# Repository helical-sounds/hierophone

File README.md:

# Hierophone

The Hierophone is an instrument designed around resonating a sheet of metal by placing it in an audio feedback loop. By changing the filtering of the audio, the phase and level of feedback, and manipulating the sheet directly, different overtones and sounds can be generated.

The name derives from ancient Greek, being the combination of ἱερά (hiera, 'holy') and φωνή (phōnē, 'voice'), together meaning "Holy Voice".

## Contact

Drop me an email at guy@rumblesan.com

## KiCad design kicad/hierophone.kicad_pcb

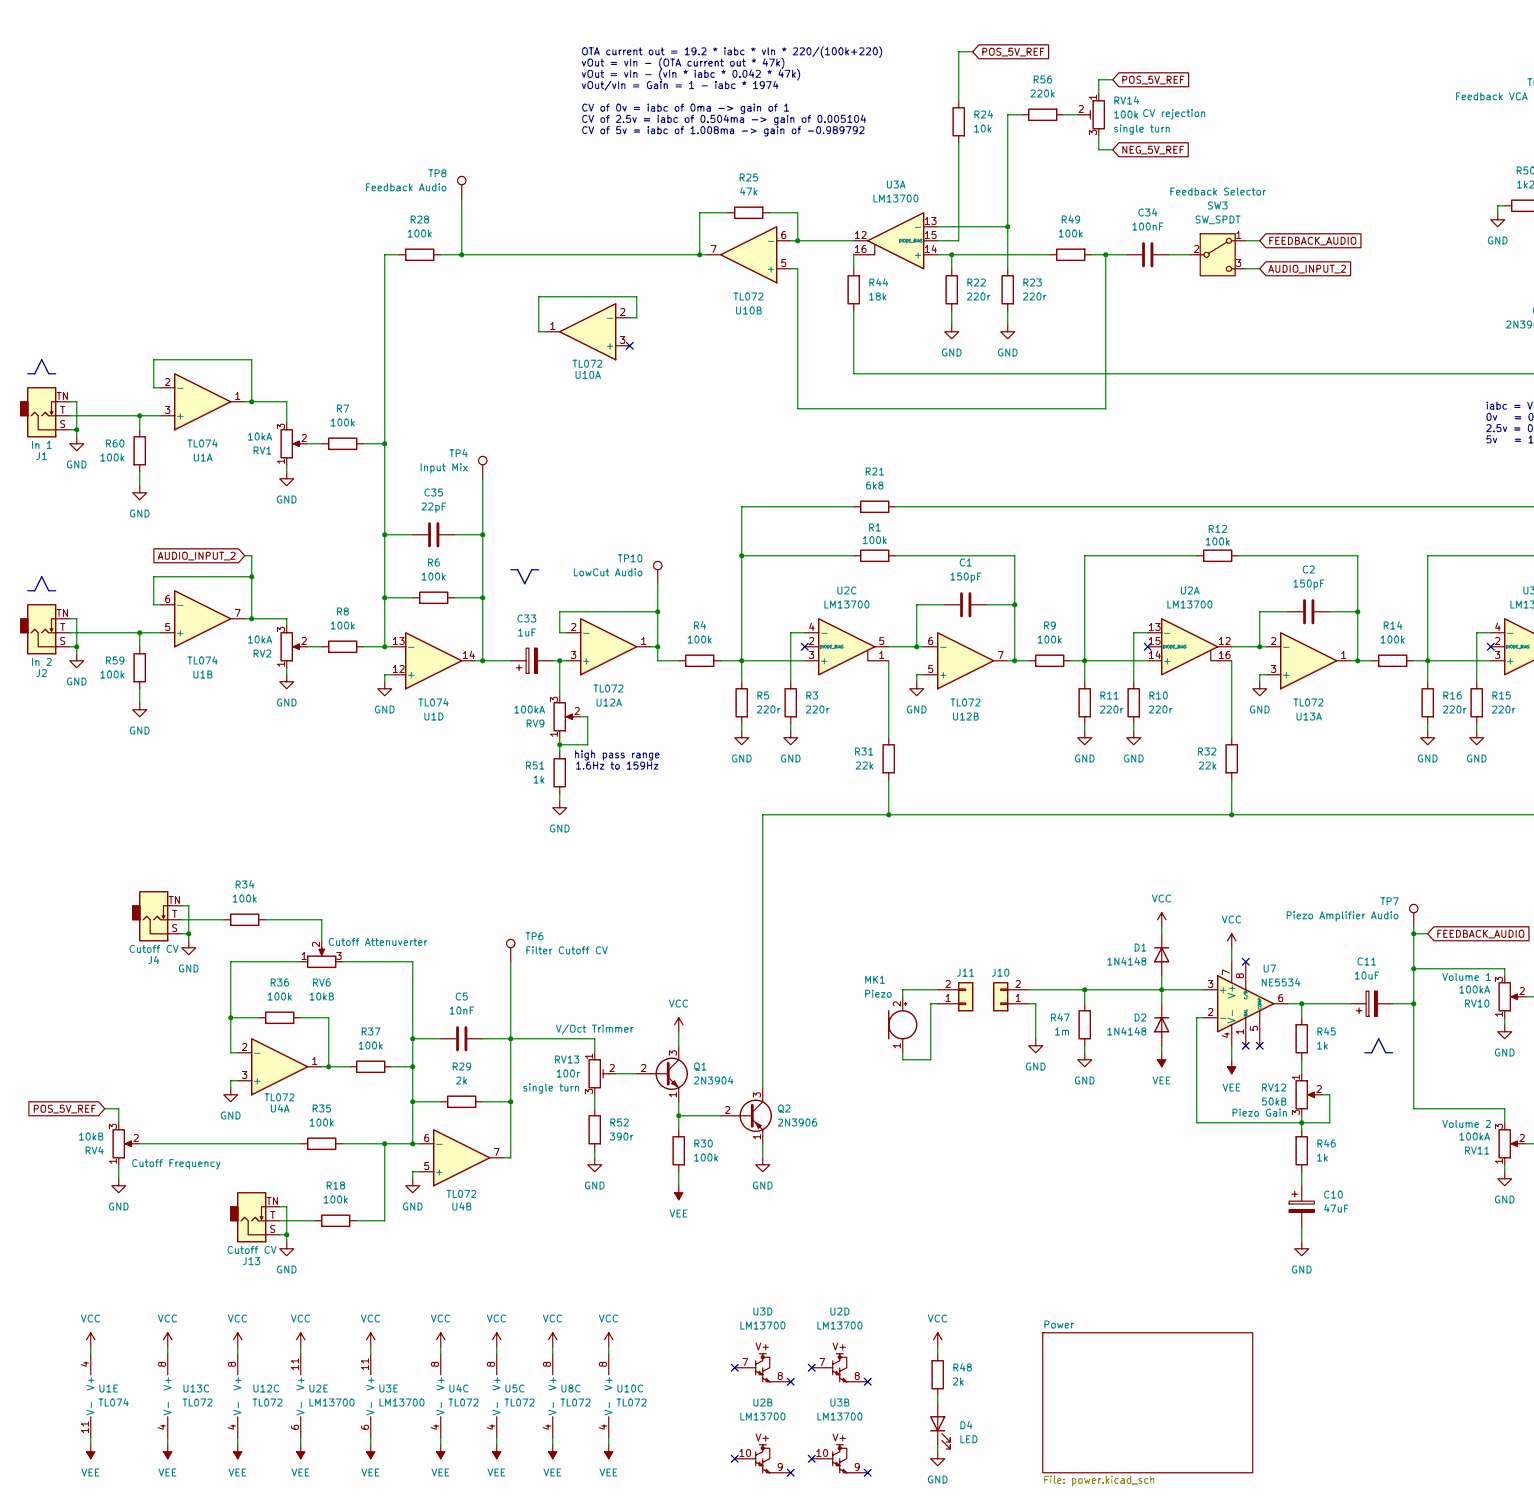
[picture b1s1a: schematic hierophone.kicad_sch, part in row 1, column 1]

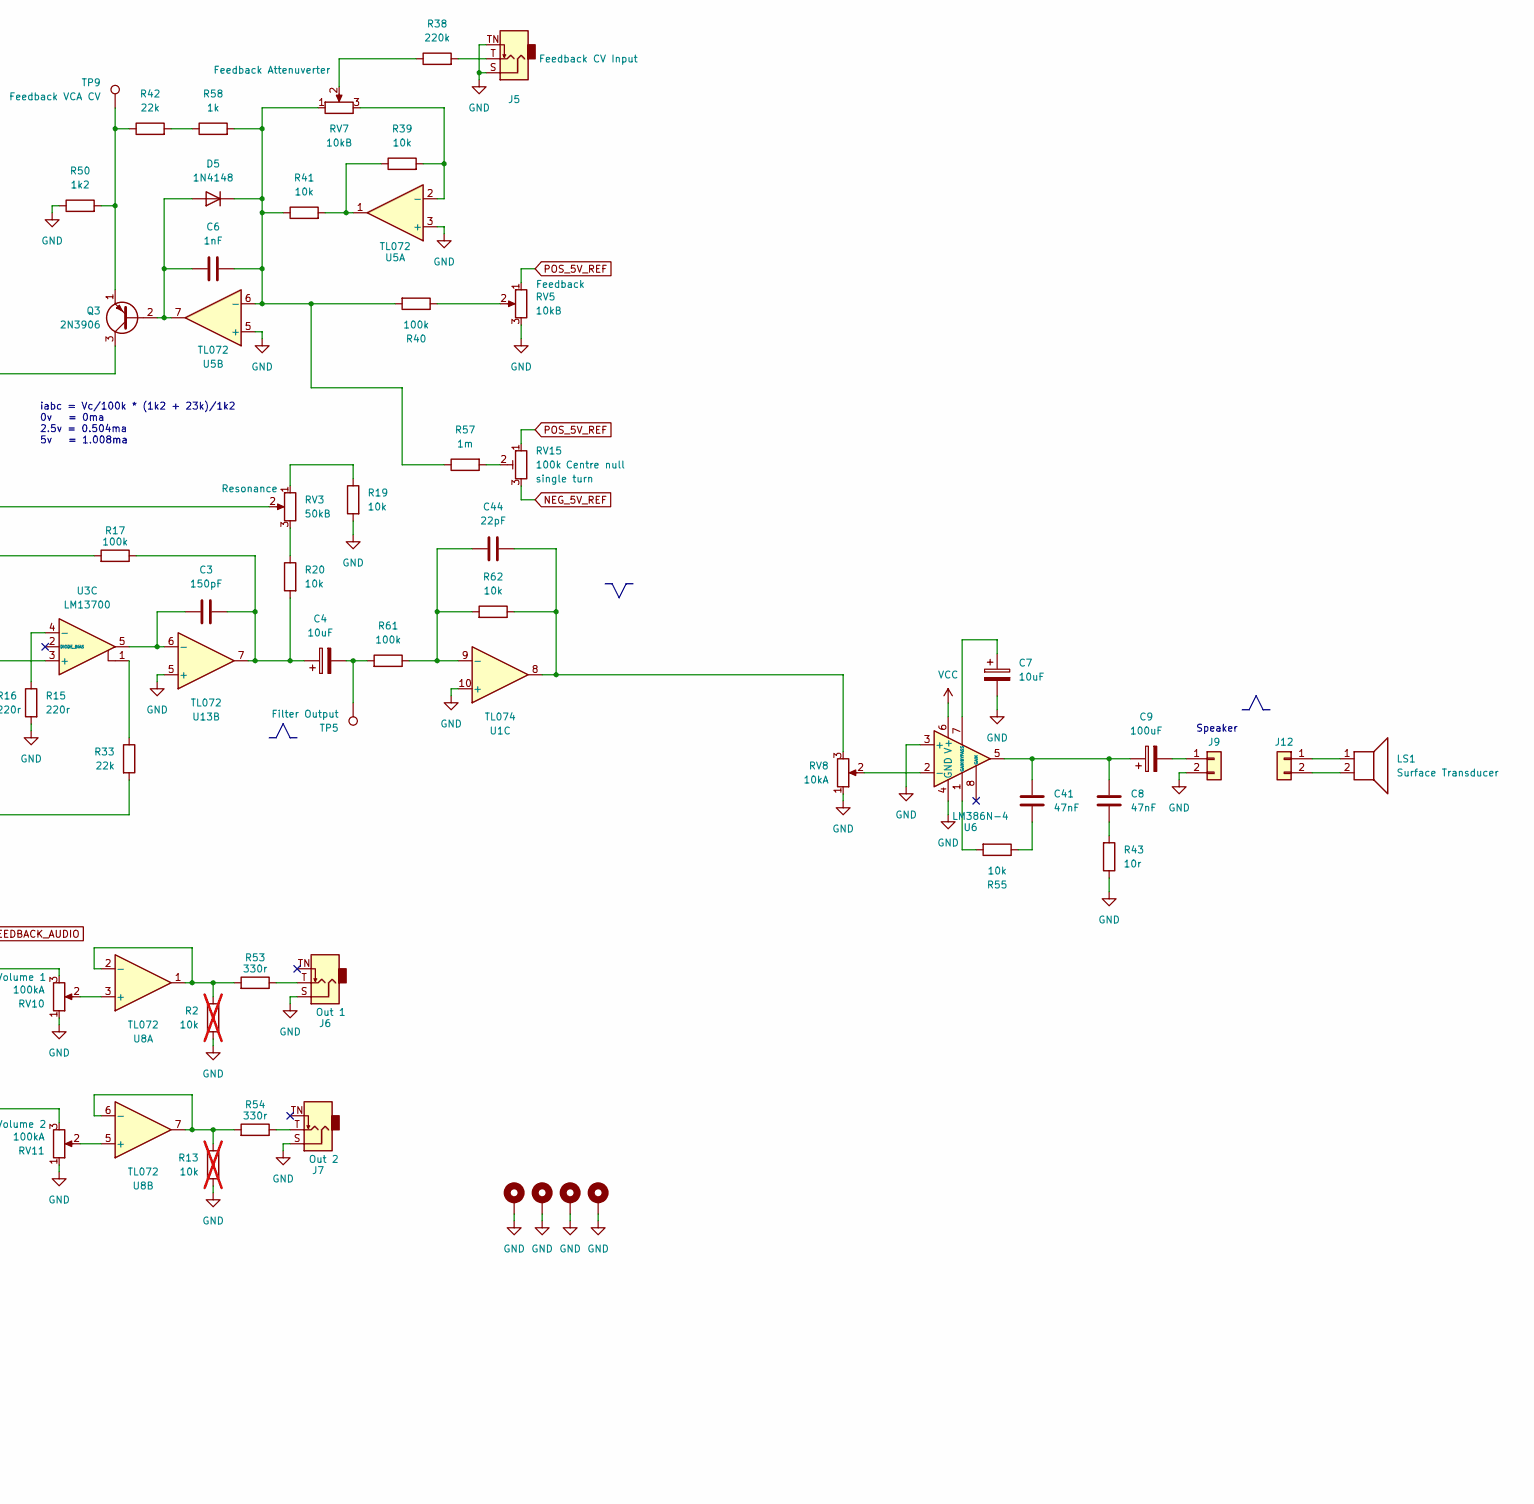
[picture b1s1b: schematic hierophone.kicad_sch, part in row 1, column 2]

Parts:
C1, C2, C3: 150pF; C_Rect_L7.0mm_W4.5mm_P5.00mm; Tolerance 5%
C4, C7, C11: 10uF; CP_Radial_D5.0mm_P2.00mm; Tolerance 20%; Voltage 50v
C5: 10nF; C_Rect_L7.0mm_W2.5mm_P5.00mm; Tolerance 5%
C6: 1nF; C_Rect_L7.0mm_W2.5mm_P5.00mm; Tolerance 5%
C8, C41: 47nF; C_Rect_L7.0mm_W2.5mm_P5.00mm; Tolerance 5%
C9: 100uF; CP_Radial_D5.0mm_P2.00mm; Tolerance 20%; Voltage 50v
C10: 47uF; CP_Radial_D5.0mm_P2.00mm; Tolerance 20%; Voltage 50v
C33: 1uF; CP_Radial_D5.0mm_P2.00mm; Tolerance 20%; Voltage 50v
C34: 100nF; C_Rect_L7.0mm_W2.5mm_P5.00mm; Tolerance 5%
C35, C44: 22pF; C_Rect_L7.0mm_W2.5mm_P5.00mm; Tolerance 5%
D1, D2, D5: 1N4148; D_DO-35_SOD27_P7.62mm_Horizontal
D4: LED; LED_D5.0mm
H1, H2, H3, H4: MountingHole_Pad; MountingHole_3.2mm_M3_Pad
J1, J2, J4, J5, J6, J7, J13: AudioJack2_SwitchT; Jack_3.5mm_QingPu_WQP-PJ398SM_Vertical
J9, J10, J11, J12: Conn_01x02; Molex_KK-254_22-05-7028_1x02_P2.54mm_Horizontal
LS1: Surface Transducer
MK1: Piezo; PinHeader_1x02_P2.54mm_Vertical
Q1: 2N3904; TO-92_Inline_Wide
Q2, Q3: 2N3906; TO-92_Inline_Wide
R1, R4, R6, R7, R8, R9, R12, R14, R17, R18, R28, R30, R34, R35, R36, R37, R40, R49, R59, R60, R61: 100k; R_Axial_DIN0207_L6.3mm_D2.5mm_P10.16mm_Horizontal; Tolerance 1%
R2, R13: 10k; R_Axial_DIN0207_L6.3mm_D2.5mm_P10.16mm_Horizontal; Tolerance 1%; not fitted
R3, R5, R10, R11, R15, R16, R22, R23: 220r; R_Axial_DIN0207_L6.3mm_D2.5mm_P10.16mm_Horizontal; Tolerance 1%
R19, R20, R24, R39, R41, R55, R62: 10k; R_Axial_DIN0207_L6.3mm_D2.5mm_P10.16mm_Horizontal; Tolerance 1%
R21: 6k8; R_Axial_DIN0207_L6.3mm_D2.5mm_P10.16mm_Horizontal; Tolerance 1%
R25: 47k; R_Axial_DIN0207_L6.3mm_D2.5mm_P10.16mm_Horizontal; Tolerance 1%
R29, R48: 2k; R_Axial_DIN0207_L6.3mm_D2.5mm_P10.16mm_Horizontal; Tolerance 1%
R31, R32, R33, R42: 22k; R_Axial_DIN0207_L6.3mm_D2.5mm_P10.16mm_Horizontal; Tolerance 1%
R38, R56: 220k; R_Axial_DIN0207_L6.3mm_D2.5mm_P10.16mm_Horizontal; Tolerance 1%
R43: 10r; R_Axial_DIN0207_L6.3mm_D2.5mm_P10.16mm_Horizontal; Tolerance 1%
R44: 18k; R_Axial_DIN0207_L6.3mm_D2.5mm_P10.16mm_Horizontal; Tolerance 1%
R45, R46, R51, R58: 1k; R_Axial_DIN0207_L6.3mm_D2.5mm_P10.16mm_Horizontal; Tolerance 1%
R47, R57: 1m; R_Axial_DIN0207_L6.3mm_D2.5mm_P10.16mm_Horizontal; Tolerance 1%
R50: 1k2; R_Axial_DIN0207_L6.3mm_D2.5mm_P10.16mm_Horizontal; Tolerance 1%
R52: 390r; R_Axial_DIN0207_L6.3mm_D2.5mm_P10.16mm_Horizontal; Tolerance 1%
R53, R54: 330r; R_Axial_DIN0207_L6.3mm_D2.5mm_P10.16mm_Horizontal; Tolerance 1%
RV1, RV2, RV8: 10kA; Potentiometer_Alpha_RD901F-40-00D_Single_Vertical
RV3, RV12: 50kB; Potentiometer_Alpha_RD901F-40-00D_Single_Vertical
RV4, RV5, RV6, RV7: 10kB; Potentiometer_Alpha_RD901F-40-00D_Single_Vertical
RV9, RV10, RV11: 100kA; Potentiometer_Alpha_RD901F-40-00D_Single_Vertical
RV13: 100r; Potentiometer_THT_Bourns_3306P_Vertical
RV14, RV15: 100k; Potentiometer_THT_Bourns_3306P_Vertical
SW3: SW_SPDT; Toggle_Switch_100SP-M2
TP4: Input Mix; TestPoint_Loop_D2.50mm_Drill1.0mm_LowProfile
TP5: Filter Output; TestPoint_Loop_D2.50mm_Drill1.0mm_LowProfile
TP6: Filter Cutoff CV; TestPoint_Loop_D2.50mm_Drill1.0mm_LowProfile
TP7: Piezo Amplifier Audio; TestPoint_Loop_D2.50mm_Drill1.0mm_LowProfile
TP8: Feedback Audio; TestPoint_Loop_D2.50mm_Drill1.0mm_LowProfile
TP9: Feedback VCA CV; TestPoint_Loop_D2.50mm_Drill1.0mm_LowProfile
TP10: LowCut Audio; TestPoint_Loop_D2.50mm_Drill1.0mm_LowProfile
U1: TL074; DIP-14_W7.62mm_Socket
U2, U3: LM13700; DIP-16_W7.62mm_Socket
U4, U5, U8, U10, U12, U13: TL072; DIP-8_W7.62mm_Socket
U6: LM386N-4; DIP-8_W7.62mm_Socket
U7: NE5534; DIP-8_W7.62mm_Socket

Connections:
AUDIO_INPUT_2: RV2.3, SW3.3 (C), U1.6 (-), U1.7
FEEDBACK_AUDIO: C11.2, RV10.3, RV11.3, SW3.1 (A), TP7.1
GND: C7.2, C10.2, D4.1 (K), H1.1, H2.1, H3.1, H4.1, J1.S, J1.TN, J2.S, J2.TN, J4.S, J4.TN, J5.S, J5.TN, J6.S, J7.S, J9.2, J10.1, J13.S, J13.TN, Q2.1 (E), R2.2, R3.1, R5.1, R10.1, R11.1, R13.2, R15.1, R16.1, R19.1, R22.1, R23.1, R43.2, R47.2, R50.2, R51.2, R52.1, R59.1, R60.1, RV1.1, RV2.1, RV4.1, RV5.3, RV8.1, RV10.1, RV11.1, U1.10 (+), U1.12 (+), U4.3 (+), U4.5 (+), U5.3 (+), U5.5 (+), U6.3 (+), U6.4 (GND), U12.5 (+), U13.3 (+), U13.5 (+); also elsewhere on the board
NEG_5V_REF: RV14.3, RV15.3; also elsewhere on the board
unnamed: C1.1, R1.1, R9.1, U12.7
unnamed: C2.1, R12.2, R14.1, U13.1
unnamed: C3.1, C4.1, R17.2, R20.1, U13.7
unnamed: C4.2, R61.1, TP5.1
unnamed: C5.2, R29.2, RV13.1, TP6.1, U4.7
unnamed: C8.2, R43.1
unnamed: C10.1, R46.2
unnamed: C11.1, R45.1, U7.6
unnamed: C33.1, C35.1, R6.2, TP4.1, U1.14
unnamed: C8.1, C9.1, C41.1, U6.5
unnamed: C41.2, R55.2
unnamed: C44.1, R62.2, RV8.3, U1.8
unnamed: D1.2 (A), D2.1 (K), J10.2, R47.1, U7.3 (+)
unnamed: D4.2 (A), R48.2
unnamed: C6.2, D5.2 (A), Q3.2 (B), U5.7
unnamed: C6.1, D5.1 (K), R40.1, R41.2, R57.2, R58.1, RV7.1, U5.6 (-)
unnamed: J4.T, R34.1
unnamed: J5.T, R38.1
unnamed: J6.T, R53.2
unnamed: J7.T, R54.2
unnamed: C9.2, J9.1
unnamed: J11.1, MK1.1 (-)
unnamed: J11.2, MK1.2 (+)
unnamed: J12.1, LS1.1
unnamed: J12.2, LS1.2
unnamed: J13.T, R18.1
unnamed: Q1.2 (B), RV13.2
unnamed: Q1.1 (E), Q2.2 (B), R30.2
unnamed: Q2.3 (C), R31.1, R32.1, R33.1
unnamed: Q3.3 (C), R44.2
unnamed: Q3.1 (E), R42.2, R50.1, TP9.1
unnamed: R7.1, RV1.2
unnamed: R8.1, RV2.2
unnamed: R19.2, RV3.1
unnamed: R20.2, RV3.3
unnamed: R21.2, RV3.2
unnamed: R25.2, R28.2, TP8.1, U10.7
unnamed: R31.2, U2.1
unnamed: R32.2, U2.16
unnamed: R33.2, U3.1
unnamed: R34.2, RV6.2
unnamed: R35.1, RV4.2
unnamed: R36.2, R37.1, U4.1
unnamed: R38.2, RV7.2
unnamed: R39.2, R41.1, U5.1
unnamed: R40.2, RV5.2
unnamed: R42.1, R58.2
unnamed: R44.1, U3.16
unnamed: R45.2, RV12.1
unnamed: R51.1, RV9.1, RV9.2
unnamed: R52.2, RV13.3
unnamed: R55.1, U6.1 (GAIN)
unnamed: R56.1, RV14.2
unnamed: R57.1, RV15.2
unnamed: C34.2, SW3.2 (B)
unnamed: J1.T, R60.2, U1.3 (+)
unnamed: RV1.3, U1.1, U1.2 (-)
unnamed: J2.T, R59.2, U1.5 (+)
unnamed: C44.2, R61.2, R62.1, U1.9 (-)
unnamed: C35.2, R6.1, R7.2, R8.2, R28.1, U1.13 (-)
unnamed: R9.2, R11.2, R12.1, U2.14 (+)
unnamed: R10.2, U2.13 (-)
unnamed: R1.2, R4.2, R5.2, R21.1, U2.3 (+)
unnamed: R3.2, U2.4 (-)
unnamed: R22.2, R49.2, U3.14 (+)
unnamed: R23.2, R56.2, U3.13 (-)
unnamed: R24.1, U3.15 (DIODE_BIAS)
unnamed: R14.2, R16.2, R17.1, U3.3 (+)
unnamed: R15.2, U3.4 (-)
unnamed: R36.1, RV6.1, U4.2 (-)
unnamed: C5.1, R18.2, R29.1, R35.2, R37.2, RV6.3, U4.6 (-)
unnamed: R39.1, RV7.3, U5.2 (-)
unnamed: RV8.2, U6.2 (-)
unnamed: C7.1, U6.7 (BYPASS)
unnamed: R46.1, RV12.2, RV12.3, U7.2 (-)
unnamed: RV10.2, U8.3 (+)
unnamed: R2.1, R53.1, U8.1, U8.2 (-)
unnamed: RV11.2, U8.5 (+)
unnamed: R13.1, R54.1, U8.6 (-), U8.7
unnamed: U10.1, U10.2 (-)
unnamed: C34.1, R49.1, U10.5 (+)
unnamed: R25.1, U3.12, U10.6 (-)
unnamed: C33.2, RV9.3, U12.3 (+)
unnamed: R4.1, TP10.1, U12.1, U12.2 (-)
unnamed: C1.2, U2.5, U12.6 (-)
unnamed: C2.2, U2.12, U13.2 (-)
unnamed: C3.2, U3.5, U13.6 (-)
POS_5V_REF: R24.2, RV4.3, RV5.1, RV14.1, RV15.1; also elsewhere on the board
VCC: D1.1 (K), Q1.3 (C), R48.1, U1.4 (V+), U2.11 (V+), U3.11 (V+), U4.8 (V+), U5.8 (V+), U6.6 (V+), U7.7 (V+), U8.8 (V+), U10.8 (V+), U12.8 (V+), U13.8 (V+); also elsewhere on the board
VEE: D2.2 (A), R30.1, U1.11 (V-), U2.6 (V-), U3.6 (V-), U4.4 (V-), U5.4 (V-), U7.4 (V-), U8.4 (V-), U10.4 (V-), U12.4 (V-), U13.4 (V-); also elsewhere on the board

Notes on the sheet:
high pass range 1.6Hz to 159Hz
Speaker
OTA current out = 19.2 * iabc * vIn * 220/(100k+220) vOut = vIn - (OTA current out * 47k) vOut = vIn - (vIn * iabc * 0.042 * 47k) vOut/vIn = Gain = 1 - iabc * 1974 CV of 0v = iabc of 0ma -> gain of 1 CV of 2.5v = iabc of 0.504ma -> gain of 0.005104 CV of 5v = iabc of 1.008ma -> gain of -0.989792
iabc = Vc/100k * (1k2 + 23k)/1k2 0v = 0ma 2.5v = 0.504ma 5v = 1.008ma

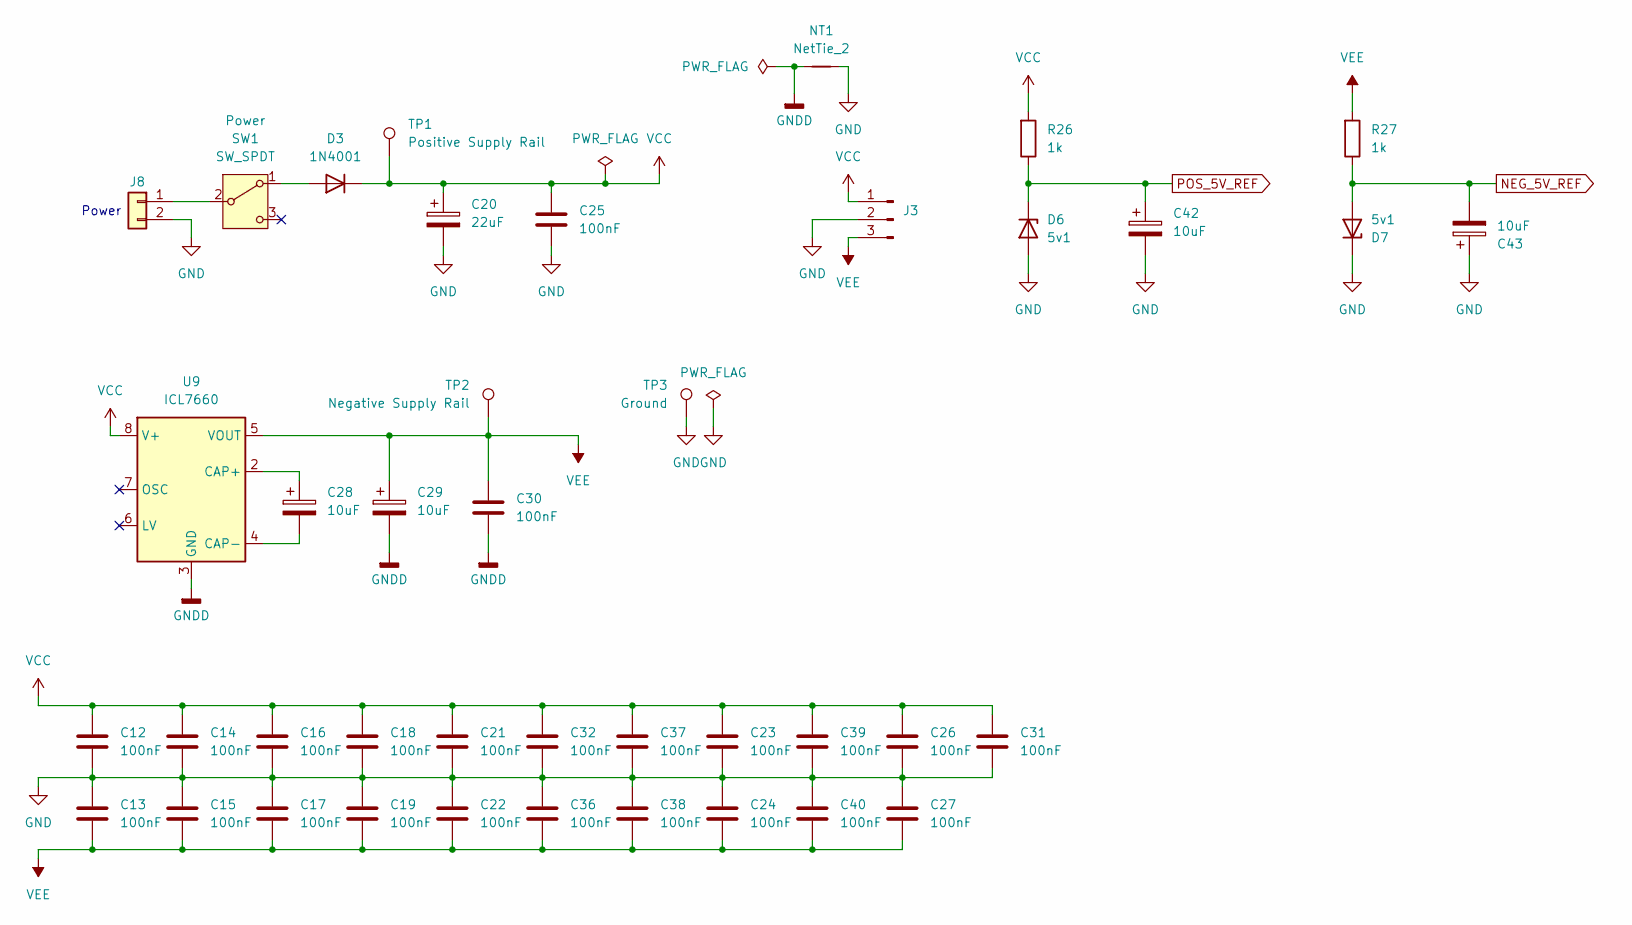
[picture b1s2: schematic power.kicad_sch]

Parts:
C12, C13, C14, C15, C16, C17, C18, C19, C21, C22, C23, C24, C25, C26, C27, C30, C31, C32, C36, C37, C38, C39, C40: 100nF; C_Rect_L7.0mm_W2.5mm_P5.00mm; Tolerance 5%
C20: 22uF; CP_Radial_D5.0mm_P2.00mm; Tolerance 20%; Voltage 50v
C28, C29, C42, C43: 10uF; CP_Radial_D5.0mm_P2.00mm; Tolerance 20%; Voltage 50v
D3: 1N4001; D_DO-41_SOD81_P10.16mm_Horizontal
D6, D7: 5v1; D_DO-41_SOD81_P10.16mm_Horizontal
J3: Conn_01x03_Pin; Molex_KK-254_22-05-7038_1x03_P2.54mm_Horizontal
J8: Conn_01x02; Molex_KK-254_22-05-7028_1x02_P2.54mm_Horizontal
NT1: NetTie_2; NetTie-2_SMD_Pad2.0mm
R26, R27: 1k; R_Axial_DIN0207_L6.3mm_D2.5mm_P10.16mm_Horizontal; Tolerance 1%
SW1: SW_SPDT; Toggle_Switch_100SP-M2
TP1: Positive Supply Rail; TestPoint_Loop_D2.50mm_Drill1.0mm_LowProfile
TP2: Negative Supply Rail; TestPoint_Loop_D2.50mm_Drill1.0mm_LowProfile
TP3: Ground; TestPoint_Loop_D2.50mm_Drill1.0mm_LowProfile
U9: ICL7660; DIP-8_W7.62mm_Socket

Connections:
GND: C12.2, C13.1, C14.2, C15.1, C16.2, C17.1, C18.2, C19.1, C20.2, C21.2, C22.1, C23.2, C24.1, C25.2, C26.2, C27.1, C31.2, C32.2, C36.1, C37.2, C38.1, C39.2, C40.1, C42.2, C43.1, D6.2 (A), D7.1 (K), J3.2, J8.2, NT1.2, TP3.1; also elsewhere on the board
GNDD: C29.2, C30.2, NT1.1, U9.3 (GND)
NEG_5V_REF: C43.2, D7.2 (A), R27.2; also elsewhere on the board
unnamed: D3.2 (A), SW1.1 (A)
unnamed: J8.1, SW1.2 (B)
unnamed: C28.1, U9.2 (CAP+)
unnamed: C28.2, U9.4 (CAP-)
POS_5V_REF: C42.1, D6.1 (K), R26.2; also elsewhere on the board
VCC: C12.1, C14.1, C16.1, C18.1, C20.1, C21.1, C23.1, C25.1, C26.1, C31.1, C32.1, C37.1, C39.1, D3.1 (K), J3.1, R26.1, TP1.1, U9.8 (V+); also elsewhere on the board
VEE: C13.2, C15.2, C17.2, C19.2, C22.2, C24.2, C27.2, C29.1, C30.1, C36.2, C38.2, C40.2, J3.3, R27.1, TP2.1, U9.5 (VOUT); also elsewhere on the board

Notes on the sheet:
Power

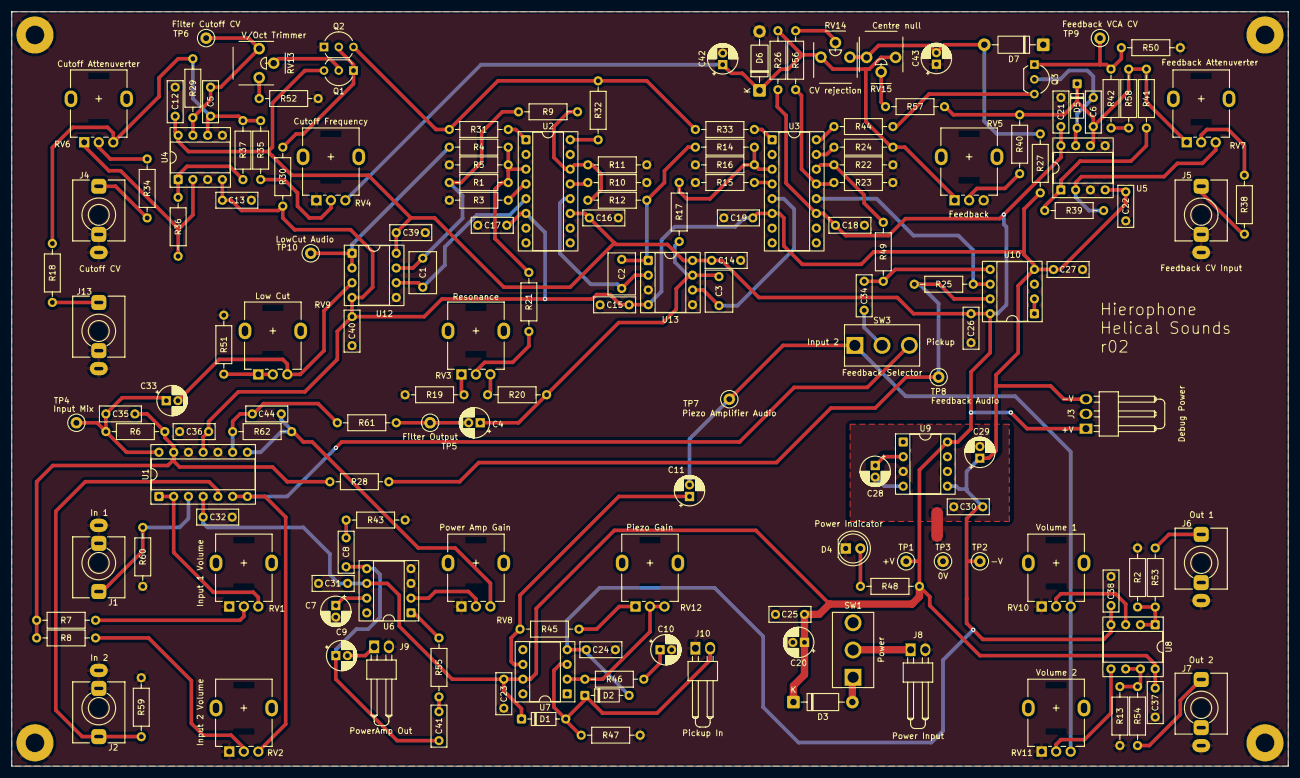
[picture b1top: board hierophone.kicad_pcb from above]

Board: 2 copper layers, 220.0 x 130.0 mm, 171 parts (0 on the bottom side), 95 nets.

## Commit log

2025-01-19 Adding rev01 gerbers
2025-02-07 Tweaking values now that build is in progress
2025-03-07 Fixing issues in schematic
2025-03-07 Fixing issues with power circuitry
2025-03-30 Adding piezo and surface transducer to schematic
2025-03-30 Updating panel with new name and layout tweak
2025-03-30 Removing old bom.ini file
2025-03-30 Updating kicad project with new name
2025-03-30 Redesign feedback VCA to be a multiplier
2025-03-30 Fixing name...
2025-03-30 Adding version info text to PCB
2025-07-14 Updating for KiCAD version 9
2025-07-16 Tweaking PCB
2025-07-18 Fixing issues with the inputs
2025-07-18 Adding volt per octave input
2025-07-18 Starting to add better documentation
2025-07-18 Adding basic signal chain diagram
2025-07-18 Adding rough design docs
2025-07-18 More pcb tweaks
2025-07-30 Make sure to specify the lm386n-4
2025-07-30 Redesign panel and PCB to have heat vents for power amp
2025-08-01 Regenerating gerbers

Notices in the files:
kicad/hierophone.kicad_pcb:
creativecommons.org/licenses/by/4.0
License: CC BY 4.0
